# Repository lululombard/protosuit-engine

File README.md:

# Protosuit Engine

**The brain of my Protogen fursuit, featuring GLSL shaders on dual round displays, LED matrix visor control, AirPlay/Spotify streaming, Doom, Super Haxagon, Bluetooth gamepads and speakers, and way more than I originally planned.**

## Demo Video

## How It Started

My friend [Miggy](https://github.com/Myggi) and I make our Protogen fursuits together, he handles 3D CAD and I handle the electronics and software. My original suit (v1) from 2023 ran a fork of [b0xcat/protocontrol](https://github.com/b0xcat/protocontrol) ([my fork](https://github.com/lululombard/protocontrol)) with 14 basic MAX7219 matrices and no sensors. I wore it at [NFC](https://nordicfuzzcon.org/) and [FBL](https://fblacklight.org/) 2024. It worked, but I wanted more.

In 2023, we found some 5-inch 1080x1080 round displays on AliExpress. Miggy designed and almost finished building a suit around them, looking back they were pretty bulky and heavy. Then in 2024 we found 4-inch 720x720 displays and that's when I jumped on board to use them for my v2 suit and his too. The project was reborn.

Miggy did all the 3D modeling to fit the displays on [b0xcat's Protato base](https://b0xcat.gumroad.com/l/protato), paired with [Coela Can't!'s WS35 LED matrices](https://coelacant1.gumroad.com/l/ws35) and [b0xcat adapters](https://coelacant1.gumroad.com/l/b0xcatadapter). In 2024 the plan was a RockPro64 with two Raspberry Pi Zero 2Ws in USB gadget mode as display drivers. Early 2025 we switched to an RPi 5 with the two Zeros, then in October 2025 I ditched the Zeros entirely and used the Pi 5's dual HDMI output directly, that's when I really restarted the project and wrote the current codebase. I started adapting Shadertoy shaders to run on it, and features just kept getting added from there.

If you're building a Protogen and want animated fin displays, feel free to adapt this for your own build!

### Thank You

- **[Miggy](https://github.com/Myggi)**: for all the 3D CAD, creating some shaders for the project, building our v1 and v2 suits together, hyping me up on everything, pitching great ideas like the now playing with lyrics, and for letting me stay at his place for weeks when we need to work on stuff
- **Kuroda**: for helping with my v1 fursuit, and for building the original b0xcat-based suits with Miggy before I joined in, and for being so welcoming and a big reason I joined the fandom in the first place
- **[b0xcat](https://github.com/b0xcat)**: for the original Protato CAD design that this project builds on, and the PETG thermoformed visor my suit is still using after all these years, I wish him the best
- **[Coela Can't!](https://github.com/coelacant1)**: for the WS35 LED matrices, the b0xcat adapter, and ProtoTracer
- **Dharsi**: for creating the original ESP32 LED circle timing game with Miggy that became Ring Ding
- **[Azavech](https://github.com/AliceDiNunno)**: for designing the score system for Ring Ding
- **Respective Shadertoy authors**: most shaders are adapted from Shadertoy, heavily modified for OpenGL ES and uniforms control, original credits are in each `.glsl` file

---

## Quick Start

1. Flash **Raspberry Pi OS Lite (64-bit)** on a microSD card with username `proto`
2. Boot the Pi and run:

```bash
sudo apt update
sudo apt upgrade -y
sudo apt dist-upgrade
sudo apt install git ansible -y
sudo reboot
```

3. Wait until the Pi reboots, and run:

```bash
git clone --recurse-submodules https://github.com/lululombard/protosuit-engine.git
cd protosuit-engine
ansible/scripts/deploy.sh
```

That's it! The system will auto-configure and start on boot.

---

## Hardware

- **Raspberry Pi 5** (4GB+ RAM)
- **Two 4-inch 720x720 round displays** with HDMI-MIPI driver boards, mounted on fursuit fins
- **Custom PCB** ([hardware/pcbs/ProtosuitDevBoard/](hardware/pcbs/ProtosuitDevBoard/)): KiCad power distribution board with 9-25V input, dual buck converters, LED matrix/strip connectors
- **USB Wi-Fi 6 + Bluetooth dongle** (RTL8851BU): handles Wi-Fi client + BT devices; built-in RPi Wi-Fi runs AP mode
- **USB microphone dongle**: for sound-reactive shader audio capture (FFT)

See **[hardware/README.md](hardware/README.md)** for PCB details, USB connections, GPIO pinout, display configuration, and Bluetooth adapter management.

---

## Features

- **GLSL Shader Animations**: Over 30 shaders with smooth cross-fade transitions, blur effects, and real-time parameter control
- **Media Playback**: Videos (exclusive), audio (stackable), synchronized playback
- **Executables**: Run shell scripts (Doom, Super Haxagon, Ring Ding) across both displays
- **Bluetooth Device Management**: Discover, pair, and connect devices via D-Bus (BlueZ API)
- **Presets**: Save and restore complete visor states (shader + uniforms + Teensy params) with a default preset that auto-restores after media playback, gamepad combo activation, and web UI management
- **Gamepad Input**: Assign controllers to displays with evdev-based input reading and MQTT forwarding
- **Audio Device Control**: Manage output devices and volume via pulsectl (PulseAudio), with auto-reconnect
- **AirPlay & Spotify Connect**: Stream audio with now-playing metadata and cover art
- **Synced Lyrics**: Real-time synchronized lyrics from lrclib.net for AirPlay and Spotify
- **Wi-Fi Management**: Dual-mode networking with AP hotspot (systemd-managed hostapd/dnsmasq), client mode via NetworkManager D-Bus, automatic NAT routing, and QR code sharing
- **ESP32 Visor**: OLED status dashboard (Pi metrics, FPS, Teensy state, DHT22 sensors), auto fan curves, notification overlay
- **Teensy LED Visor**: ProtoTracer 3D LED rendering with face animations, audio visualization, and effects
- **Web Control Interface**: Browser-based control with live preview, physics-based sliders, and performance monitoring
- **PSP Remote Controller**: PSP homebrew app as wireless gamepad over MQTT
- **Custom PCB**: KiCad-designed power distribution board with LED matrix/strip connectors

---

## Web Interface

Open your browser to `http://<raspberry-pi-ip>`

| Page | URL | Description |
|------|-----|-------------|
| Dashboard | `/` | Shader selector, parameter sliders, live preview, FPS monitor, visor status |
| Virtual Controller | `/controller` | Mobile-friendly gamepad UI for testing inputs |
| Bluetooth & Audio | `/bluetooth` | Device scanning, pairing, controller assignment, audio device selection |
| Cast Settings | `/cast` | AirPlay/Spotify enable/config, now-playing with cover art, synced lyrics |
| Networking | `/networking` | Wi-Fi client/AP config, QR code sharing, service health |

The dashboard includes a visor panel with fan curve editor and Teensy LED menu controls (face, brightness, color, effects).

---

## Architecture

Ten independent Python services communicating via MQTT, plus shared utilities for logging, D-Bus, and systemd control. See **[engine/README.md](engine/README.md)** for the full services table, shared modules, configuration reference, and complete MQTT API.

- **MQTT**: All inter-service messaging under `protogen/fins/*` and `protogen/visor/*`
- **D-Bus**: BlueZ (Bluetooth), systemd (service control), PulseAudio (audio sinks)
- **Serial**: ESP32 ↔ Pi (tab-separated with CRC-8 checksum, 921,600 baud), ESP32 ↔ Teensy (text commands)

**Supporting services:** `xserver` (X11), `mosquitto` (MQTT broker), `pulseaudio` (audio server)

---

## Repository Layout

```
protosuit-engine/
├── engine/                  # Python services + shared modules (see engine/README.md)
│   ├── audiobridge/         #   Audio device/volume management
│   ├── bluetoothbridge/     #   Bluetooth discovery/pairing
│   ├── castbridge/          #   AirPlay, Spotify Connect, lyrics
│   ├── config/              #   Config loader module
│   ├── controllerbridge/    #   Gamepad input forwarding
│   ├── data/                #   OUI MAC address lookup table
│   ├── espbridge/           #   ESP32 serial bridge
│   ├── launcher/            #   Media/executable launcher
│   ├── networkingbridge/    #   Wi-Fi client/AP management
│   ├── renderer/            #   OpenGL shader renderer
│   ├── utils/               #   Shared modules (MQTT, logger, D-Bus, etc.)
│   └── web/                 #   Flask web interface + static assets
├── firmware/                # Embedded firmware (see firmware/README.md)
│   ├── esp32/               #   ESP32 firmware (PlatformIO C++)
│   ├── prototracer/         #   Teensy LED visor firmware (git submodule)
│   └── psp-controller/      #   PSP homebrew MQTT controller (C/PSP SDK)
├── hardware/                # PCB and hardware designs (see hardware/README.md)
│   └── pcbs/
│       └── ProtosuitDevBoard/  # KiCad PCB design
├── ansible/                 # Ansible deployment playbooks and templates
├── assets/                  # Shaders (.glsl), audio, video, apps, executables (.sh)
├── scripts/                 # Utility scripts
├── tests/                   # Integration tests
├── config.yaml              # Main configuration file
├── protosuit_engine.py      # Development launcher (all services in one process)
└── requirements.txt         # Python dependencies
```

---

## Firmware

- **[ESP32](firmware/esp32/)**: PlatformIO C++ firmware for visor sensors, fan control, OLED display, and MQTT/Teensy serial bridge
- **[ProtoTracer / Teensy 4.0](firmware/prototracer/)**: real-time 3D LED rendering engine (git submodule, fork of [coelacant1/ProtoTracer](https://github.com/coelacant1/ProtoTracer))
- **[PSP Controller](firmware/psp-controller/)**: PSP homebrew app as wireless MQTT gamepad

```bash
./firmware/esp32/build_and_upload.sh          # ESP32: build, upload, restart espbridge
./firmware/prototracer/build_and_upload.sh    # Teensy: build, upload via loader GUI
```

See **[firmware/README.md](firmware/README.md)** for modules, serial protocol, fan curves, Teensy menu parameters, and build details.

---

## Service Management

```bash
# Check status
sudo systemctl status protosuit-renderer
sudo systemctl status protosuit-launcher
sudo systemctl status protosuit-web
sudo systemctl status protosuit-bluetoothbridge
sudo systemctl status protosuit-audiobridge
sudo systemctl status protosuit-controllerbridge
sudo systemctl status protosuit-castbridge
sudo systemctl status protosuit-networkingbridge
sudo systemctl status protosuit-espbridge

# View logs
sudo journalctl -u protosuit-renderer -f

# Restart a service
sudo systemctl restart protosuit-renderer
```

---

## Creating Custom Shaders

Create GLSL shaders in `assets/shaders/`:

```glsl
#version 300 es
precision highp float;

uniform float iTime;
uniform vec2 iResolution;
uniform float speed;        // MQTT-controllable
uniform vec3 color1;        // MQTT-controllable

in vec2 v_fragCoord;
out vec4 fragColor;

void main() {
    vec2 uv = v_fragCoord / iResolution;
    vec3 col = color1 * sin(uv.x * 10.0 + iTime * speed);
    fragColor = vec4(col, 1.0);
}
```

Add to `config.yaml` and control via MQTT. See [engine/README.md](engine/README.md) for examples.

---

## Testing

```bash
./tests/test_mqtt_inputs.sh    # Tests Doom, Super Haxagon, Ring Ding inputs
```

---

## Development

```bash
cd ~/protosuit-engine
source env/bin/activate
python protosuit_engine.py     # All services in one process (dev only)
```

For production, use systemd services (see [Service Management](#service-management)).

---

## Troubleshooting

### Displays not showing content
```bash
sudo systemctl status xserver
sudo systemctl status protosuit-renderer
DISPLAY=:0 xrandr --query
```

### MQTT commands not working
```bash
sudo systemctl status mosquitto
mosquitto_sub -t "protogen/#" -v    # Monitor all topics
```

### ESP32 not connecting
```bash
sudo journalctl -u protosuit-espbridge -f
ls -la /dev/ttyUSB0                  # Check serial device exists
```

### Teensy upload issues
```bash
lsusb | grep Teensy                  # Only visible in bootloader mode
killall teensy                       # Kill stuck uploader UI
./firmware/prototracer/build_and_upload.sh    # Retry
```

For more help, [open an issue on GitHub](https://github.com/lululombard/protosuit-engine/issues).

---

## Future Plans

### Hardware
New PCB integrating all components:
- SMD power circuitry instead of off-the-shelf buck converter modules
- ESP32 module directly on-board instead of a dev board
- Raspberry Pi Compute Module mounted in the visor (fan-cooled area) instead of a full RPi 5 in the fin (soft temp limit currently set to 60°C to avoid PETG warping due to no airflow)
- Custom display driver circuitry instead of separate HDMI-MIPI boards
- Custom LED matrix PCB for fins instead of many cut/soldered LED strips

### Features
- **PS Vita Control**: Migrate from PSP to PS Vita. WPA1 support required by PSP is too much of a hassle. Be able to switch presets, control launcher, etc.
- **Shader image/video support**: load images and videos as shader inputs (textures)
- **Single web page**: Ditch the separate controller/bluetooth/networking/cast and integrate it on the single web page with modals
- **Web UI refactor**: Terminal style, desktop with folders (presets, shaders, visor), needs to be phone compatible

### Reliability
- **Use same uniform names**: Ability to sync HueF/HueB for color1/color2 when available, same speed names, etc...

---

## License

This project is licensed under the [GNU Affero General Public License v3.0](LICENSE) (AGPL-3.0), matching the [ProtoTracer](https://github.com/coelacant1/ProtoTracer) license.

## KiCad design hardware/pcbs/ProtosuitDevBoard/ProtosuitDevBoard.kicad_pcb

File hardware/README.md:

# Protosuit Engine Hardware Documentation

This document covers all hardware aspects of the Protosuit Engine project, including the custom PCB, USB connections, GPIO pinout, displays, and Bluetooth adapter management.

## Bill of Materials

Everything you need to buy to build the suit.

| Component | Qty | Notes |
|-----------|-----|-------|
| **Computing** | | |
| Raspberry Pi 5 (4GB+) | 1 | Main processor |
| ESP32 dev board (Wemos D1 Mini ESP32) | 1 | Visor sensors, fan, OLED, LED strips |
| Teensy 4.0 | 1 | WS35 LED matrix rendering (ProtoTracer) |
| **Displays** | | |
| 4" 720x720 round display + HDMI-MIPI driver board | 2 | Search "wisecoco 4 inch 720 round" on AliExpress |
| 0.96" SSD1306 128x64 OLED (I2C) | 1 | Visor status dashboard, connected to ESP32 |
| **Sensors** | | |
| DHT22 temperature/humidity sensor | 1 | Visor temp monitoring for auto fan curve |
| APDS-9960 proximity sensor | 1 | Boop sensor, connected to Teensy I2C |
| MPU6050 6-axis IMU | 1 | Gyroscope + accelerometer, on-board (currently unused) |
| MAX9814 microphone amplifier | 1 | Teensy audio-reactive features |
| **LED Matrices & Strips** | | |
| WS35 LED matrix panels | 4 | [Coela Can't! design](https://coelacant1.gumroad.com/l/ws35), requires trace cut (see [WS35 Panel Modification](#ws35-panel-modification)) |
| SK6812 LED strip, 300 LEDs | 1 | Upper arch |
| WS2812B LED strip, 60 LEDs | 2 | Left and right fins |
| WS2812B LED strip, 40 LEDs | 2 | Left and right ears |
| **Audio & Connectivity** | | |
| USB microphone dongle | 1 | Sound-reactive shader audio capture (FFT) |
| RTL8851BU USB Wi-Fi 6 + Bluetooth dongle | 1 | Wi-Fi client mode + all BT devices |
| **Cooling** | | |
| Noctua NF-A4x10 5V PWM fan | 1 | 40x10mm, 4-pin PWM, visor ventilation |
| **Power** | | |
| USB-C PD power bank (20V output) | 1 | Powers the entire suit |
| USB-C PD 20V to XT60 cable | 1 | Connects power bank to PCB |
| 5V 5A buck converter (TPS54X60) | 1 | Powers RPi + displays (25W) |
| 5V 8A buck converter (CRDC2580) | 1 | Powers Teensy, ESP32, all LEDs (40W) |
| **Cables** | | |
| HDMI FFC cable, 15cm | 1 | Left fin display |
| HDMI FFC cable, 80cm | 1 | Right fin display |
| **PCB & On-Board Components** | | |
| ProtosuitDevBoard PCB | 1 | Order from gerbers in `pcbs/ProtosuitDevBoard/gerber_v1_0/` |
| 2-pin screw terminal block | 2 | Power in (20V) + RPi power out (5V) |
| 3-pin screw terminal block | 9 | WS35 matrices (4) + LED strips (5) |
| JST 4-pin connector (male, PCB) | 4 | I2C headers: OLED, boop sensor, gyro, expansion |
| JST 3-pin connector (male, PCB) | 2 | MAX9814 mic + DHT22 sensor |
| Fan connector header | 1 | 4-pin for Noctua fan |
| Potentiometer (small trim, 200Ω) | 9 | Inline on LED data lines (4 matrices + 5 strips), can be replaced with ~68Ω resistors (50-150Ω range works) |
| 2N3904 NPN transistor | 1 | Fan PWM control |
| 4.7kΩ resistor | 1 | |
| 2.2kΩ resistor | 1 | |
| 10kΩ resistor | 1 | |
| 100kΩ resistor | 1 | |
| **Connectors & Tools** | | |
| JST connectors (female, 4-pin) + crimping tool | - | I2C cables (OLED, boop sensor, etc.) |
| JST connectors (female, 3-pin) | - | MAX9814 mic + DHT22 cables |
| Ferrule crimps + ferrule crimping tool | - | For screw terminal and power connections |

## PCB Design (pcbs/ProtosuitDevBoard/)

The main PCB is designed in **KiCad 8.0** and serves as the central power distribution and interconnect board for the suit.

### Power Input

- **9-25V input** via XT60 connector
- Powered by a USB-C PD 20V to XT60 cable from a power bank, minimizing power loss between the battery and PCB

### Power Distribution

| Converter | Rating | Load |
|-----------|--------|------|
| 5V 5A low-ESR buck-boost | 25W | Shared between RPi and 2x LCD displays |
| 5V 8A buck-boost | 40W | Main PCB powering Teensy 4.0, ESP32, WS35 matrices, and LED strips |

### LED Connectors

All LED connectors are screw terminals with ferrule crimps. Power input and 5V output connectors also use ferrule crimps.

- **4x [WS35 LED matrix](https://coelacant1.gumroad.com/l/ws35) connectors** (3-pin screw terminals, Coela Can't! design)
- **5x LED strip connectors** (3-pin screw terminals):
  - 2x fins
  - 2x ears
  - 1x upper arch

### WS35 Panel Modification

Each WS35 panel has two halves, each with its own 5V, GND, and signal pins. By default, the DOUT of the last LED on the first half is connected to DIN of the first LED on the second half, daisy-chaining both halves.

**You must saw/cut the trace between the two halves.** Since there is no level shifter on the PCB, the Teensy's 3.3V signal cannot override the 5V signal coming out of DOUT on the first half. Cutting the connection allows each half to be driven independently from its own DIN pin.

### Other Connectors (JST)

- I2C header
- MAX9814 microphone input (for Teensy audio-reactive features)
- DHT22 temperature/humidity sensor connector (for ESP32)

### Custom Footprint Libraries

Custom KiCad footprint library in `Aliexpress.pretty/`:

| Footprint | Description |
|-----------|-------------|
| ESP32_MIN132_V_1_0_0 | ESP32 module |
| DC_DC_5V_5A_TPS54X60 | 5V 5A buck converter |
| DC_DC_5V_8A_CRDC2580 | 5V 8A buck converter |
| LEVEL_SHIFTER_TXS0108E | 8-channel level shifter (not used in PCB 1.1, wrong type of shifter, bypassed in 1.0) |
| GYRO_MPU6050 | 6-axis IMU (gyroscope + accelerometer), on-board but currently unused |
| TEENSY_4_0 | Teensy 4.0 module (modified from original) |

### Board Status

The current board (v1.1) is a **validation prototype** using off-the-shelf modules (buck converters, ESP32 dev board) with no SMD components, making it quite bulky. The goal is to eventually move to SMD power circuitry, an ESP32 module directly on-board, a Raspberry Pi Compute Module, and custom display driver circuitry instead of HDMI-MIPI boards.

### Manufacturing and Project Files

- Gerber manufacturing files in `gerber_v1_0/`
- `.kicad_sch` -- schematic
- `.kicad_pcb` -- PCB layout
- `.kicad_pro` -- project file

## USB Connections

### Pi to Teensy 4.0 -- USB without 5V power

- **VUSB=VIN jumper configuration**, no cut trace on Teensy
- Teensy is powered from the main PCB 5V 8A rail, NOT from Pi USB
- Only appears in `lsusb` while in bootloader/upload mode
- Used exclusively for firmware uploads

### Pi to ESP32 -- USB with 5V power

- CH341 USB-to-serial chip needs USB bus power
- CH341 is NOT powered by the ESP32 main 5V rail
- Always visible in `lsusb` as `/dev/ttyUSB0`
- Used for bidirectional serial communication (921,600 baud)

### USB Microphone Dongle

- Used for sound-reactive shader audio capture
- Captured by renderer via the sounddevice library (FFT)

### USB Wi-Fi 6 + Bluetooth Dongle

- RTL8851BU chipset, handles both Wi-Fi and Bluetooth
- Wi-Fi: used for client mode (internet access); built-in RPi Wi-Fi is used for AP mode
- Bluetooth: used for all BT devices (gamepads, audio); see [Bluetooth Adapter Management](#bluetooth-adapter-management)
- The built-in RPi radio has issues running AP + BT simultaneously, this dongle avoids that entirely

## ESP32 GPIO Pinout

| GPIO | Function | Direction | Notes |
|------|----------|-----------|-------|
| 27 | DHT22 Temperature/Humidity | Input | +/-0.5C, +/-2% RH accuracy |
| 33 | PWM Fan Control | Output | 21.6 kHz, 8-bit (0-255), inverted duty cycle |
| 35 | Fan Tachometer | Input | FALLING edge interrupts, 2 pulses/revolution |
| 21 | I2C SDA (OLED Display) | Bidirectional | SSD1306 128x64 monochrome |
| 22 | I2C SCL (OLED Display) | Bidirectional | |
| 5 | LED Strip (Upper Arch) | Output | SK6812 |
| 18 | LED Strip (Left Ear) | Output | WS2812B |
| 19 | LED Strip (Right Fin) | Output | WS2812B, 60 LEDs |
| 23 | LED Strip (Left Fin) | Output | WS2812B, 60 LEDs |
| 26 | LED Strip (Right Ear) | Output | WS2812B |
| 16 | UART RX (Teensy) | Input | 921,600 baud |
| 17 | UART TX (Teensy) | Output | 921,600 baud |

## Display Configuration

- 2x 4-inch 720x720 round displays (search "wisecoco 4 inch 720 round" on AliExpress) with HDMI-MIPI driver boards, mounted on fursuit fins
- Left display: rotated 90 degrees clockwise
- Right display: rotated 90 degrees counter-clockwise
- Extended desktop spanning both displays
- Managed by X11 via xrandr (configured by Ansible)

### 3D Model

3D files are available in the `3D/` folder to help model the display mounting:

- `Screen.stl` — mesh for slicers (PrusaSlicer, Bambu Studio, etc.)
- `screen.step` — parametric STEP file for CAD software (FreeCAD, Fusion 360, etc.)

They were modeled directly on b0xcat's fursuit head, so their position in space may be off depending on your build.

A few tips when designing around this model:

- **Print tolerance:** use at least 0.2mm tolerance to ensure the display fits and can be removed without forcing on it.
- **Leave clearance above the screen:** any pressure applied from above (when putting on the head or from a plastic piece resting on top) is transferred directly to the screen, which is quite fragile. Make sure there is a small gap above the display glass so mechanical stress goes to the frame, not the panel.
- **Connector clearance:** the model includes a small rectangle representing the display's flex connector. Leave enough room around it! do not crush or sharply bend it. While the connector is flexible, it should not be overly stressed.

## Bluetooth Adapter Management

The RPi's built-in radio shares Wi-Fi and Bluetooth on the same chip. Running AP mode + Bluetooth simultaneously causes issues for both: degraded AP performance and unreliable BT connections. The [RTL8851BU USB dongle](#usb-wi-fi-6--bluetooth-dongle) handles both Wi-Fi client and Bluetooth, and can manage Wi-Fi + 3 BT devices (2 controllers + 1 speaker) simultaneously without issues.

Ideally, use separate adapters for gamepads and audio to prevent bandwidth conflicts (a shared adapter can cause audio stuttering and controller input lag), but a single USB dongle works well for most setups.

Configure in `config.yaml` under `bluetoothbridge.adapters`:

| Adapter Role | Default | Description |
|--------------|---------|-------------|
| gamepads | hci1 (USB dongle) | Adapter for controllers |
| audio | hci1 (USB dongle) | Adapter for speakers/headphones |

### Useful Commands

```bash
# List available adapters
bluetoothctl list

# Show adapter details
hciconfig -a

# Enable USB adapter
sudo rfkill unblock bluetooth && sudo hciconfig hci1 up
```

## OLED Display (on ESP32)

- SSD1306 128x64 monochrome OLED via I2C
- Updated every loop iteration (~1 second)
- Library: U8g2 (page buffer mode)

### Information Displayed

- Pi connection status
- Controller count
- Current shader
- Fan percentage
- Fan mode (Auto/Manual)
- RPM
- Temperature
- Humidity

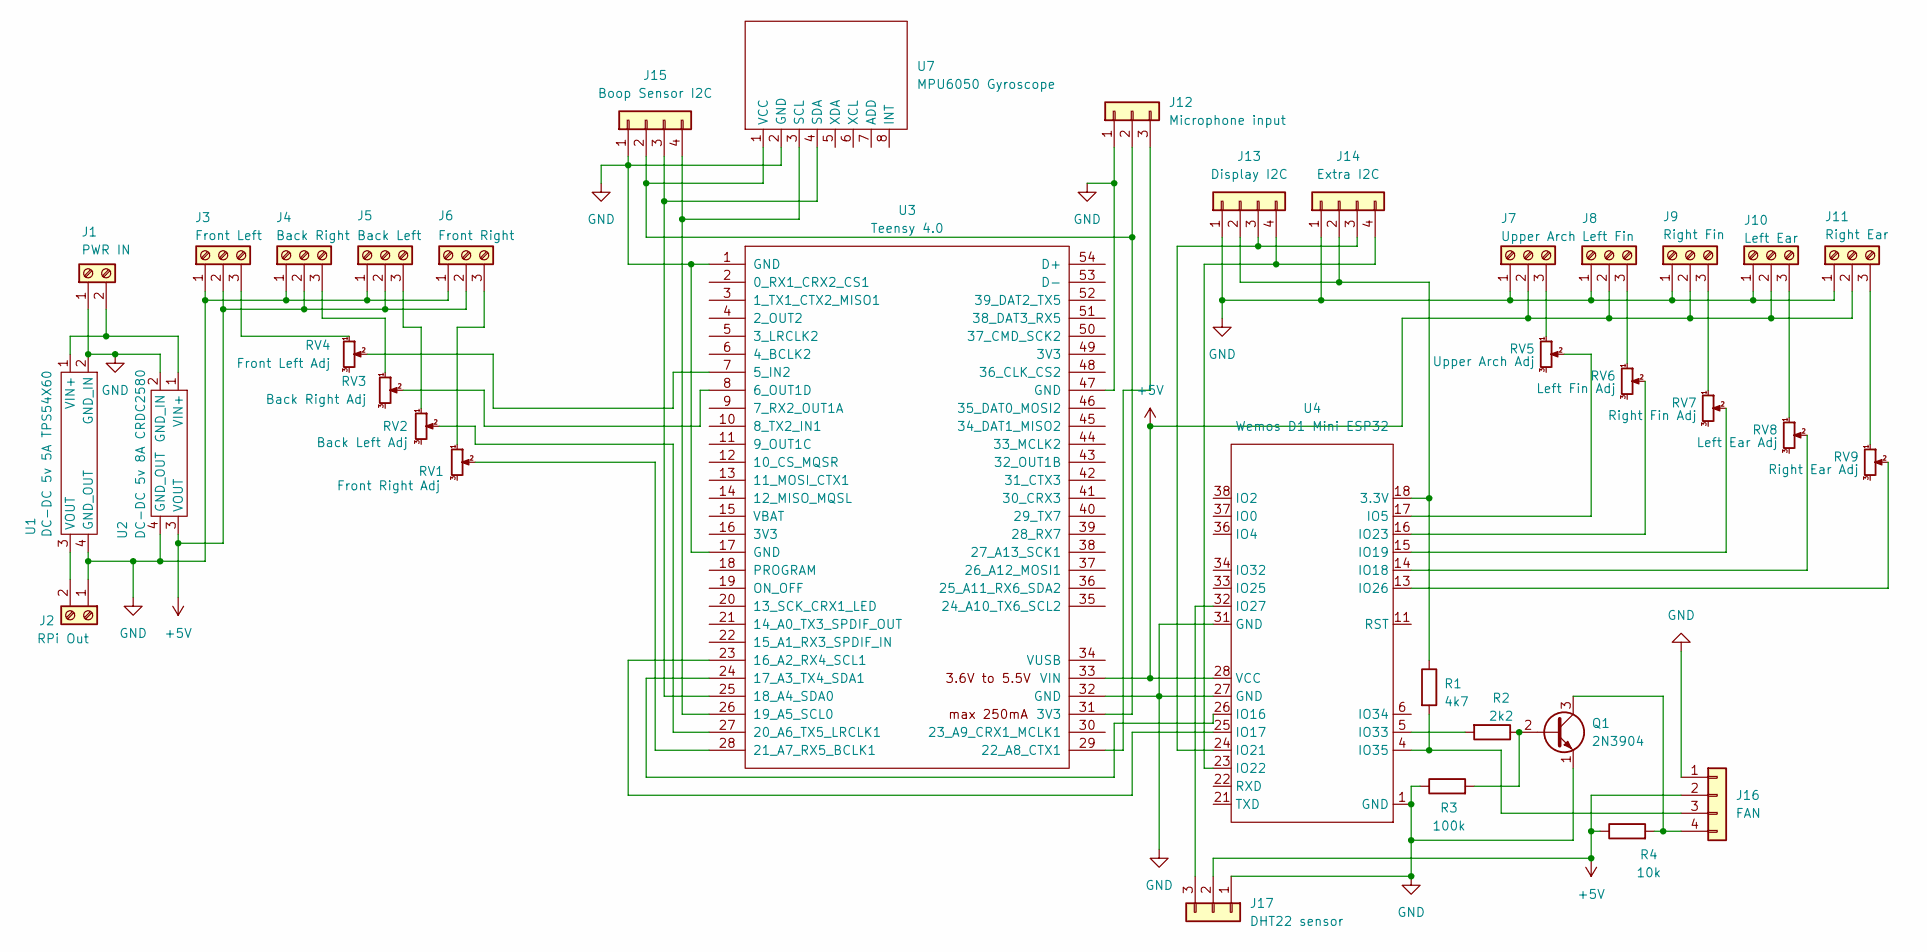
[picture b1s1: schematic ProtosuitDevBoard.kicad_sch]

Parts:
J1: PWR IN; TerminalBlock_MaiXu_MX126-5.0-02P_1x02_P5.00mm
J2: RPi Out; TerminalBlock_MaiXu_MX126-5.0-02P_1x02_P5.00mm
J3: Front Left; TerminalBlock_MaiXu_MX126-5.0-03P_1x03_P5.00mm
J4: Back Right; TerminalBlock_MaiXu_MX126-5.0-03P_1x03_P5.00mm
J5: Back Left; TerminalBlock_MaiXu_MX126-5.0-03P_1x03_P5.00mm
J6: Front Right; TerminalBlock_MaiXu_MX126-5.0-03P_1x03_P5.00mm
J7: Upper Arch; TerminalBlock_MaiXu_MX126-5.0-03P_1x03_P5.00mm
J8: Left Fin; TerminalBlock_MaiXu_MX126-5.0-03P_1x03_P5.00mm
J9: Right Fin; TerminalBlock_MaiXu_MX126-5.0-03P_1x03_P5.00mm
J10: Left Ear; TerminalBlock_MaiXu_MX126-5.0-03P_1x03_P5.00mm
J11: Right Ear; TerminalBlock_MaiXu_MX126-5.0-03P_1x03_P5.00mm
J12: Microphone input; JST_XH_B3B-XH-A_1x03_P2.50mm_Vertical
J13: Display I2C; JST_XH_B4B-XH-A_1x04_P2.50mm_Vertical
J14: Extra I2C; JST_XH_B4B-XH-A_1x04_P2.50mm_Vertical
J15: Boop Sensor I2C; JST_XH_B4B-XH-A_1x04_P2.50mm_Vertical
J16: FAN; FanPinHeader_1x04_P2.54mm_Vertical
J17: DHT22 sensor; JST_XH_B3B-XH-A_1x03_P2.50mm_Vertical
Q1: 2N3904; TO-92_Inline
R1: 4k7; R_Axial_DIN0207_L6.3mm_D2.5mm_P2.54mm_Vertical
R2: 2k2; R_Axial_DIN0207_L6.3mm_D2.5mm_P2.54mm_Vertical
R3: 100k; R_Axial_DIN0207_L6.3mm_D2.5mm_P2.54mm_Vertical
R4: 10k; R_Axial_DIN0207_L6.3mm_D2.5mm_P2.54mm_Vertical
RV1: Front Right Adj; Potentiometer_Bourns_3296W_Vertical
RV2: Back Left Adj; Potentiometer_Bourns_3296W_Vertical
RV3: Back Right Adj; Potentiometer_Bourns_3296W_Vertical
RV4: Front Left Adj; Potentiometer_Bourns_3296W_Vertical
RV5: Upper Arch Adj; Potentiometer_Bourns_3296W_Vertical
RV6: Left Fin Adj; Potentiometer_Bourns_3296W_Vertical
RV7: Right Fin Adj; Potentiometer_Bourns_3296W_Vertical
RV8: Left Ear Adj; Potentiometer_Bourns_3296W_Vertical
RV9: Right Ear Adj; Potentiometer_Bourns_3296W_Vertical
U1: DC-DC 5v 5A TPS54X60; DC_DC_5V_5A_TPS54X60
U2: DC-DC 5v 8A CRDC2580; DC_DC_5V_8A_CRDC2580
U3: Teensy 4.0; TEENSY_4_0
U4: Wemos D1 Mini ESP32; ESP32_MIN132_V_1_0_0
U7: MPU6050 Gyroscope; GYRO_MPU6050

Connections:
+5V: J3.2, J4.2, J5.2, J6.2, J7.2, J8.2, J9.2, J10.2, J11.2, J16.2, J17.2, R4.1, U2.3 (VOUT), U3.33 (VIN), U4.28 (VCC)
GND: J1.1, J2.1, J3.1, J4.1, J5.1, J6.1, J7.1, J8.1, J9.1, J10.1, J11.1, J12.1, J13.1, J14.1, J15.1, J16.1, J17.1, Q1.1 (E), R3.1, U1.2 (GND_IN), U1.4 (GND_OUT), U2.2 (GND_IN), U2.4 (GND_OUT), U3.1 (GND), U3.17 (GND), U3.32 (GND), U3.47 (GND), U4.1 (GND), U4.2 (NC), U4.27 (GND), U4.31 (GND), U7.2 (GND)
unnamed: J1.2, U1.1 (VIN+), U2.1 (VIN+)
unnamed: J2.2, U1.3 (VOUT)
unnamed: J3.3, RV4.1
unnamed: J4.3, RV3.1
unnamed: J5.3, RV2.1
unnamed: J6.3, RV1.1
unnamed: J7.3, RV5.1
unnamed: J8.3, RV6.1
unnamed: J9.3, RV7.1
unnamed: J10.3, RV8.1
unnamed: J11.3, RV9.1
unnamed: J12.2, J15.2, U3.31 (3V3), U7.1 (VCC)
unnamed: J12.3, U3.29 (22_A8_CTX1)
unnamed: J13.2, J14.2, R1.1, U4.18 (3.3V)
unnamed: J13.3, J14.3, U4.24 (IO21)
unnamed: J13.4, J14.4, U4.23 (IO22)
unnamed: J15.3, U3.25 (18_A4_SDA0), U7.4 (SDA)
unnamed: J15.4, U3.26 (19_A5_SCL0), U7.3 (SCL)
unnamed: J16.3, R1.2, U4.4 (IO35)
unnamed: J16.4, Q1.3 (C), R4.2
unnamed: J17.3, U4.32 (IO27)
unnamed: Q1.2 (B), R2.1, R3.2
unnamed: RV4.2, U3.7 (5_IN2)
unnamed: RV3.2, U3.8 (6_OUT1D)
unnamed: U3.23 (16_A2_RX4_SCL1), U4.25 (IO17)
unnamed: U3.24 (17_A3_TX4_SDA1), U4.26 (IO16)
unnamed: RV2.2, U3.27 (20_A6_TX5_LRCLK1)
unnamed: RV1.2, U3.28 (21_A7_RX5_BCLK1)
unnamed: RV5.2, U4.17 (IO5)
unnamed: RV8.2, U4.14 (IO18)
unnamed: RV7.2, U4.15 (IO19)
unnamed: RV6.2, U4.16 (IO23)
unnamed: RV9.2, U4.13 (IO26)
unnamed: R2.2, U4.5 (IO33)

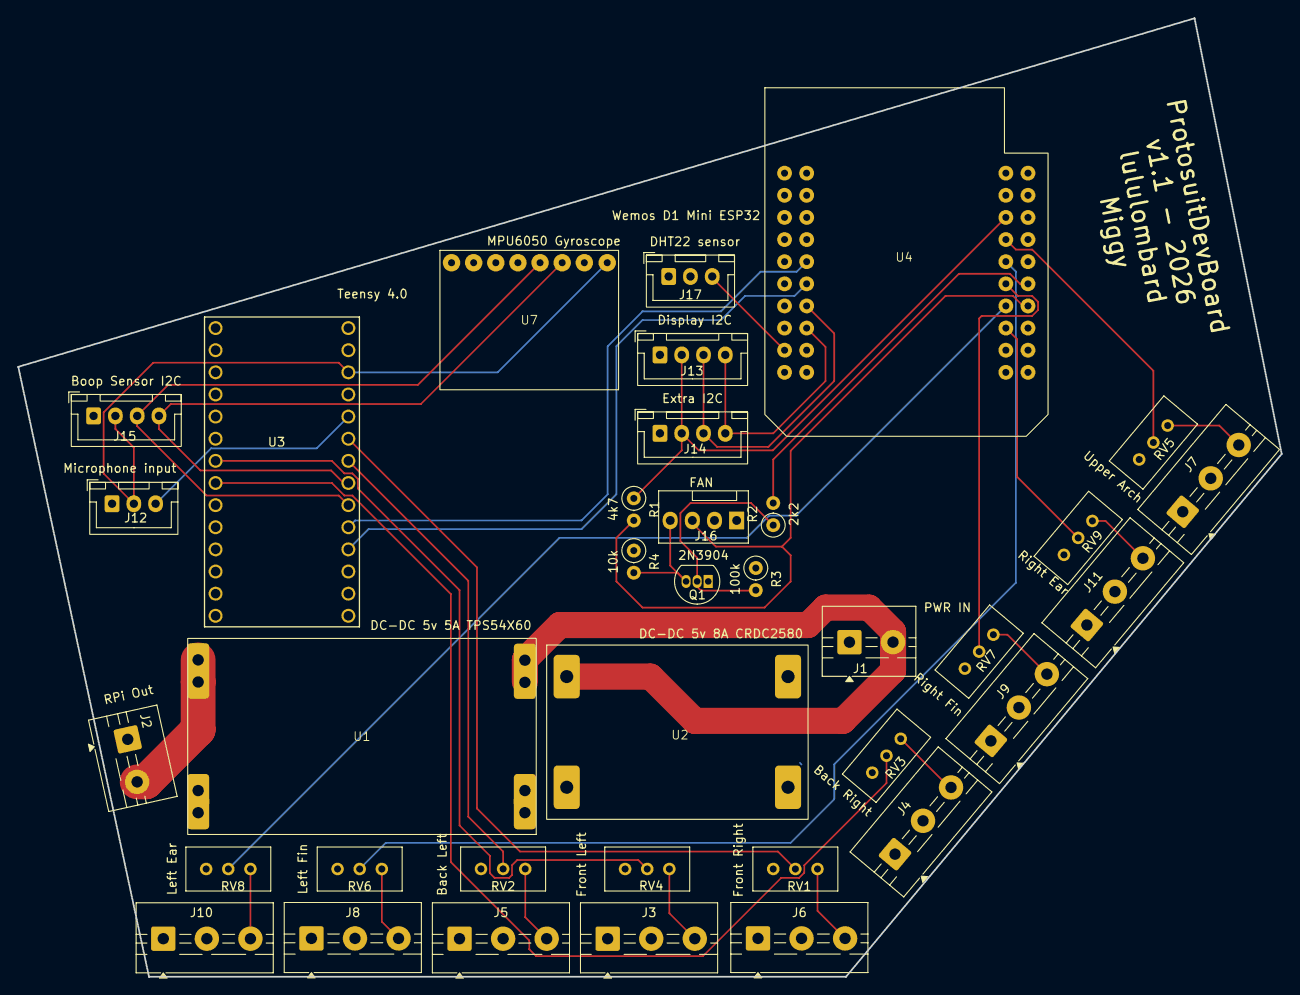
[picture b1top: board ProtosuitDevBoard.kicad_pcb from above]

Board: 4 copper layers, 145.0 x 110.0 mm, 36 parts (0 on the bottom side), 36 nets.

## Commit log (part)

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2025-02-13 First release
2025-02-13 Fix missing directory
2025-02-13 Fix service name
2025-02-13 Update reboot process
2025-02-13 Add missing systemd service
2025-02-13 Try configuring interfaces in a different way
2025-02-13 Fix network generation on hub
2025-02-13 Add inter pi zero communication
2025-02-13 Fix routes
2025-02-13 Add missing instructions
2025-02-14 Add WAN access from the Pi zeroes
2025-02-14 Fix iptables restore
2025-02-14 Fix NetworkManager conflicts
2025-02-16 Add matchbox doc
2025-02-16 Fix username
2025-02-16 Split Ansible scripts
2025-02-16 Rename some roles
2025-02-16 Fix host vars
2025-02-16 Add zsh setup
2025-02-16 Add missing user@host
2025-02-16 Add step to use new shell
2025-02-16 Fix order of zsh plugins
2025-02-16 Fix config to run Matchbox without root user
2025-02-16 Add tmux
2025-02-16 Add Rust compile and deployment
2025-02-16 Fix Rust install
2025-02-16 Fix missing crossbuild packages
2025-02-16 Add missing deps for arm 32 bits
2025-02-16 Add yet another missing lib
2025-02-16 Fix wrong package name
2025-02-16 Use armhf toolchain
2025-02-16 Force new toolchain
2025-02-16 Use SDL2 armhf packages
2025-02-16 Add missing deps
2025-02-16 Add missing packages
2025-02-16 Remove libwayland-cursor-dev
2025-02-16 Fix missing toolchain
2025-02-16 Remove libxdbe-dev
2025-02-16 Add wayland-scanner
2025-02-16 Fix building
2025-02-16 Disable wayland
2025-02-16 Disable audio (at least for now)
2025-02-16 Fix broken packages
2025-02-16 Disable KMS/DRM
2025-02-16 Remove IBus
2025-02-16 Point to IBUS
2025-02-16 Try to disable default features
2025-02-17 Re-write ansible playbook
2025-02-17 Fix missing dir
2025-02-17 Fix path
2025-02-17 Fix missing env
2025-02-17 Fix file name
2025-02-17 Fix invalid instruction to copy via SSH
2025-02-17 Remove unclutter (high CPU usage)
2025-02-17 Add MQTT server
2025-02-17 Fix MQTT status
2025-02-17 Fix missing rebuild
2025-02-17 Add screen rotation
2025-02-17 Remove fbdev
2025-02-17 Try another rotation
2025-02-17 Handle display rotation on firmware level
2025-02-17 Add graceful shutdown
2025-02-17 Fix cargo config
2025-02-17 Fix missing shutdown signals
2025-02-17 Fix SIGTERM
2025-02-17 Fix display rotation
2025-02-17 Fix how we rotate
2025-02-18 Compile for arm v6
2025-02-18 Add Pi Zero 1 support
2025-02-18 Better target armv6
2025-02-18 Revert to armv7
2025-02-21 Refined README networking steps
2025-02-21 Add script to monitor USB setups
2025-02-21 Add rule for end0
2025-02-21 Fix Configure display rotation in cmdline.txt
2025-02-21 Fix how we install rustup
2025-02-21 Add build-essential
2025-02-21 add gcc-arm-linux-gnueabihf
2025-02-22 Fix cross-compile issues
2025-02-22 Fix display config
2025-02-22 Fix typo oopsie
2025-02-22 Remove useless reboot step
2025-02-22 Add options to follow display settings
2025-02-22 Add even more flags
2025-02-22 Add support for display rotation inside the sdl manager
2025-02-22 Adding debug message
2025-02-22 Fix how we start the idle display
2025-02-22 Try another way
2025-02-22 Fix warnings
2025-02-22 Re-organized playbooks
2025-02-22 Fix missing pointer
2025-02-22 Fix error
2025-02-22 Fix wrong type
2025-02-22 Add debugging message
2025-02-22 Simplify code
2025-02-23 Add scenes
2025-02-23 Use a single TTF context
2025-02-23 Fix two scenes started at the same time
2025-02-23 Add more MQTT debug
2025-02-23 Fix switching logic
2025-02-23 Fix rotation
2025-02-23 Fix orientation
2025-02-23 Fix how we start stuff
2025-02-23 Fix rendering issues
2025-02-23 Add non-X11 option
2025-02-23 Fix missing OS callbacks
2025-02-23 Fix issue on RpiOS
2025-02-23 Revert
2025-02-23 Use pointers
2025-02-23 Cleanup
2025-02-23 Switch to C
2025-02-23 Update build process
2025-02-23 Fix issues
2025-02-23 Fix path for armhf
2025-02-23 Fix step to restart afeter deploy
2025-02-23 Fix restart policy
2025-02-23 Smoother animations
2025-03-08 Try Enlightenment
2025-10-12 Testing python version
2025-10-12 Complete project rewrite: Replace 3-Pi setup with single-Pi Python implementation
    - Removed all Ansible deployment scripts for multi-Pi setup
    - Removed Rust-based SDL engine for Pi Zeros
    - Added Python-based single Pi implementation
    - New shader-based display system
    - Simplified architecture for single device deployment
2025-10-17 First alpha
2025-10-18 MQTT refactor
2025-10-18 Fix example
2025-10-19 Fix Doom
2025-10-22 Add SuperHaxagon and Ring Ding + MQTT input and web page for games
2025-10-23 Higher perf
2025-10-23 WIP - PSP Controller
2025-10-23 Actually install PSP SDK
2025-10-23 Add PSP controller
2025-10-24 Beter PSP doc
2025-10-25 Add My Ordinary Life video
2025-11-11 Add ytdl script
2025-11-11 Add volume control
2026-01-17 Add PCB
2026-01-22 Final dev board
2026-01-23 Remap apps to A and B only
2026-01-23 Part 2 of edits for new keys
2026-01-23 Update doc
2026-01-23 Bluetooth controller support
2026-01-24 Better handling of BT errors
2026-01-24 Make Bluetooth more generic
2026-01-24 Re-compiled PSP app for new controls
2026-01-24 Add Bluetooth audio support
2026-01-24 Fix launcher issue
2026-01-24 Fix volume and auto reconnect
2026-01-25 Robust bluetooth and audio
2026-01-25 Fix fallback on broken pulseaudio
2026-01-25 Fix controller buffer replay
2026-01-25 Fix slow shutdown
2026-01-25 Fix rfkilled interface
2026-01-26 Add B button to go back to ring ding menu
2026-01-26 Add network manager
2026-01-26 Fix NAT
2026-01-27 Completely fixed networking
2026-01-28 Faster startup
2026-01-28 Faster program start
2026-01-28 Add casting service
2026-01-28 Add avahi mdns backend
2026-01-28 Update documentation
2026-01-29 Add absolute solver, improve video playback performance
2026-01-30 New shaders + credit for previous shaders
2026-02-04 Update Wi-Fi drivers
2026-02-04 Fix wlan0 -> wlan1 client switch
2026-02-05 Fix BT and Wi-Fi
2026-02-05 Score system for Ring Ding
2026-02-05 Add ESP32 project and coms
2026-02-07 Add current playing on web
2026-02-07 Karaoke!
2026-02-07 Add now playing exec
2026-02-07 Fix multiple sync issues
2026-02-07 Add blurred background
2026-02-08 Add new infinite mirror shader
2026-02-08 Use DBUS for Castbridge
2026-02-08 Fix title out of bounds
2026-02-08 Rotating lyrics!
2026-02-08 Finished now_playing!
2026-02-08 Fix lyrics
2026-02-08 Less alpha for previous lyrics
2026-02-08 Larger text
2026-02-08 Remove unused vars
2026-02-08 Fix topic
2026-02-09 Working coms with Teensy
2026-02-10 Add web UI for Teensy
2026-02-11 Bump pillow from 10.4.0 to 12.1.1
    Bumps [pillow](https://github.com/python-pillow/Pillow) from 10.4.0 to 12.1.1.
    - [Release notes](https://github.com/python-pillow/Pillow/releases)
    - [Changelog](https://github.com/python-pillow/Pillow/blob/main/CHANGES.rst)
    - [Commits](https://github.com/python-pillow/Pillow/compare/10.4.0...12.1.1)
    ---
    updated-dependencies:
2026-02-11 Major BT refactor
2026-02-11 Fix bluetooth controllers
2026-02-12 Doc update + Airplay volume sync
2026-02-12 Add prototracer reference
2026-02-12 Migrate from raspotify to spotifyd for 2-way volume
2026-02-12 Fix inconsistencies on ProtoTracer
2026-02-12 Repo refactor
2026-02-12 Major repo refactor
2026-02-13 Refactor networking stack
2026-02-14 De-hardcode HDMI displays
2026-02-15 Sync ESP32 LEDs with ProtoTracer
2026-02-15 Remove broken config
2026-02-15 Document LED GPIO
2026-02-15 Add system bridge
2026-02-15 Add option to restart ProtoTracer and ESP32 from web UI
2026-02-15 WebRTC live stream
2026-02-15 Single notification class
2026-02-15 Fallback for ESPBridge
2026-02-16 Fix Spotify setting volume to 100% on play
2026-02-16 Add reload config option
2026-02-16 ESP32 display refactor
2026-02-16 Fix Dualshock 4 compatibility
2026-02-16 Add presets features
2026-02-16 Add volume debounce
2026-02-16 Fix Spotify volume
2026-02-16 Log reason why we change volume
2026-02-16 Override remote volume
2026-02-17 Add ESP32 override
2026-02-18 Show preset instead of shader priority
2026-02-18 NFC Day 1 DLC
2026-02-18 New FFT logic
2026-02-18 Better vsync
2026-02-20 Add French baguette
2026-02-28 Updated documentation
2026-03-04 Lyrics fallback
2026-03-04 Add NFC YouTube video to README
2026-03-04 Bump flask from 3.1.2 to 3.1.3
    Bumps [flask](https://github.com/pallets/flask) from 3.1.2 to 3.1.3.
    - [Release notes](https://github.com/pallets/flask/releases)
    - [Changelog](https://github.com/pallets/flask/blob/main/CHANGES.rst)
    - [Commits](https://github.com/pallets/flask/compare/3.1.2...3.1.3)
    ---
    updated-dependencies:
2026-03-14 Add display 3D model files (STL and STEP)
2026-03-14 Add 3D model notes and files to display configuration section
2026-04-05 Add custom transition system with shader reorganization
    - Reorganize shaders into animations/ and transition/ subdirectories
    - Add 7 transition shaders: crossfade, iris, split, glitch, dissolve, scan, mosaic
    - Consolidate transition duration to a single source of truth (config.yaml default,
    overridable via MQTT). previously hardcoded in multiple places across the renderer
    - Update renderer, config, and web UI to add transition animation selection and duration setup
2026-04-05 Fix configloader() in reload_config of renderer.py
2026-04-05 Move french_baguette.glsl to animations folder
2026-04-05 Persist transition config across restarts via retained MQTT status topic
2026-04-06 update to one shader, renderer now supports video & image rendering, optimisation of renderer, config.yaml now supports declaration of resources for shader
2026-04-13 Bump pillow from 12.1.1 to 12.2.0
    Bumps [pillow](https://github.com/python-pillow/Pillow) from 12.1.1 to 12.2.0.
    - [Release notes](https://github.com/python-pillow/Pillow/releases)
    - [Changelog](https://github.com/python-pillow/Pillow/blob/main/CHANGES.rst)
    - [Commits](https://github.com/python-pillow/Pillow/compare/12.1.1...12.2.0)
    ---
    updated-dependencies:
